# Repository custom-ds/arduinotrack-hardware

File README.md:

# ArduinoTrack APRS Tracker
The Project: Traveler ArduinoTrack flight controller is an Arduino-compatible board that includes a GPS, temp/pressure sensor, and options for a VHF transmitter module or a off-board transmitter.

For more information about the ArduinoTrack, visit the [Project: Traveler](https://www.projecttraveler.org/arduinotrack/arduinotrack-controller) website.

Firmware for the ArduinoTrack must be programmed via a hardware programmer.

[ArduinoTrack Firmware](https://github.com/custom-ds/arduinotrack-firmware)

## Buy an ArduinoTrack
Assembled ArduinoTracks can be purchased online from [Custom Digital Services](https://www.customdigitalservices.net/high-altitude-ballooning/buy-an-arduinotrack).

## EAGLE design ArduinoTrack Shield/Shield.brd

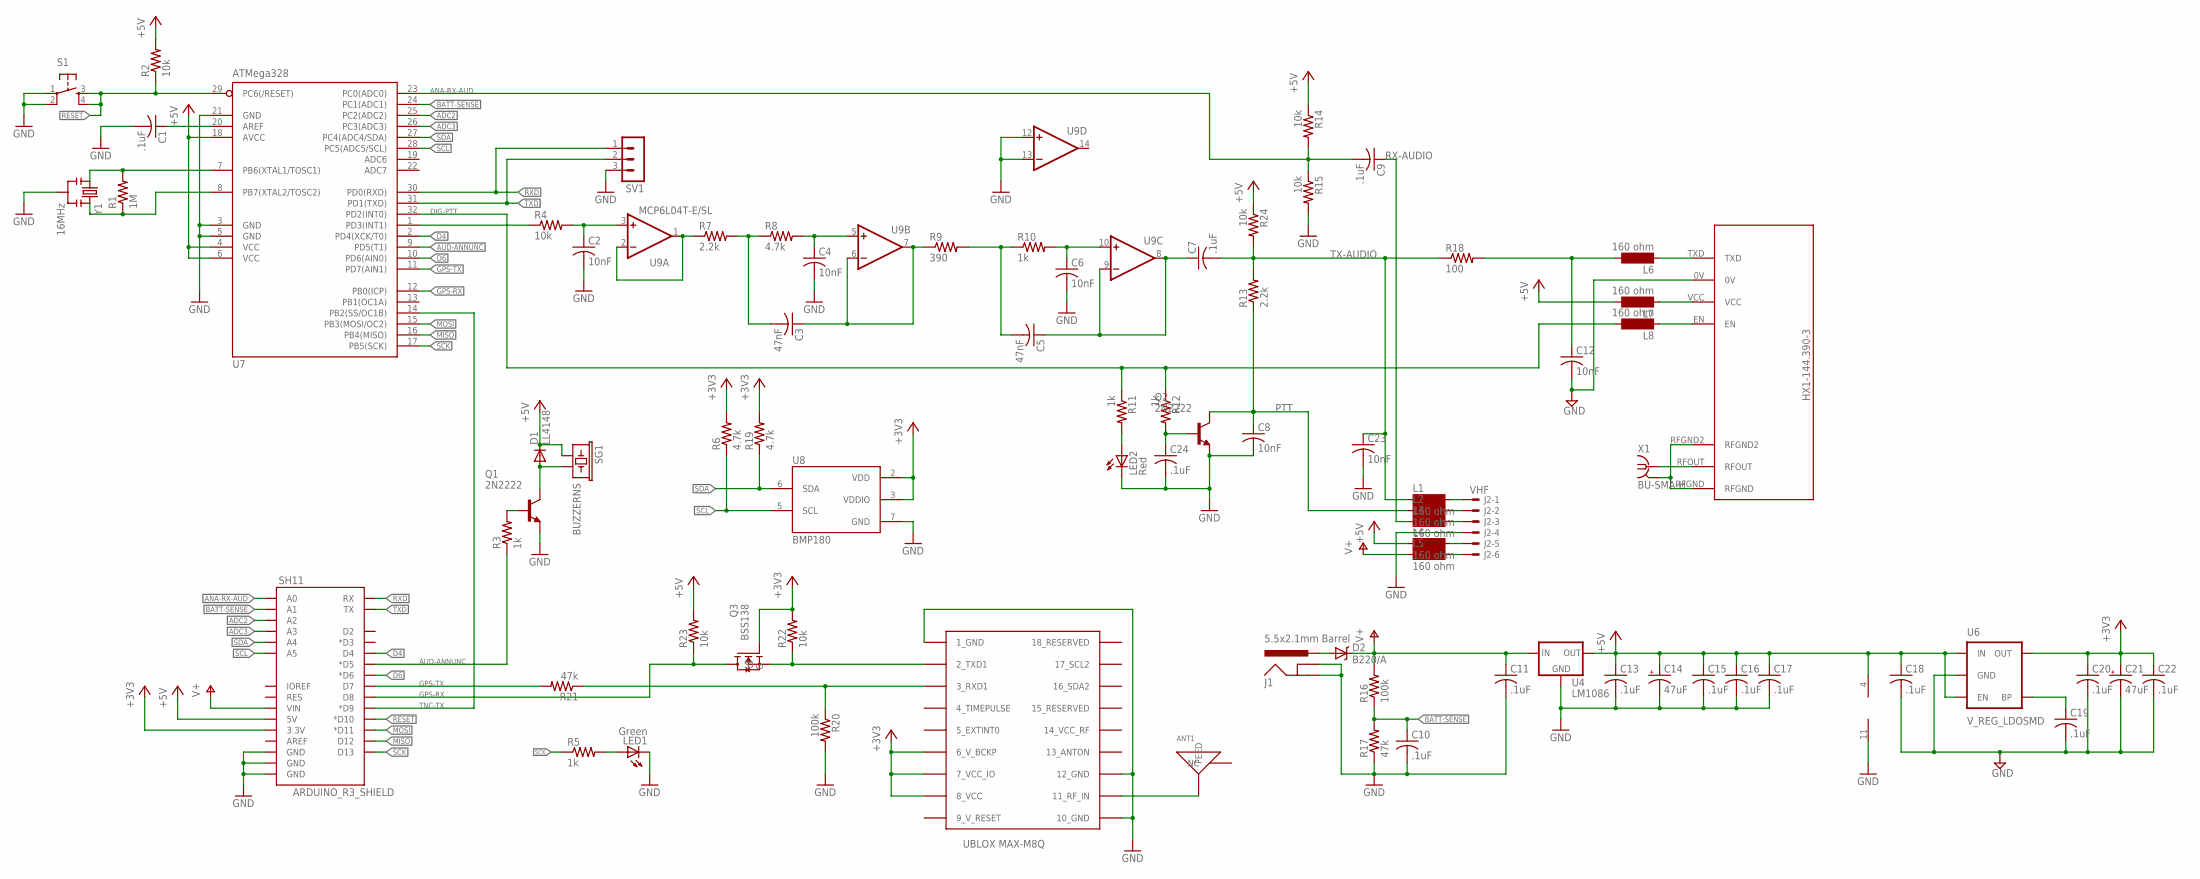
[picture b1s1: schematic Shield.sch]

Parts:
ANT1: GPS_ANT_SMDBAR; 1575AT43A40; DIGIKEY 712-1003-1-ND
C1, C7, C9, C10, C11, C13, C15, C16, C17, C18, C19, C20, C22, C24: .1uF; C0805; DIGIKEY 311-1361-1-ND
C2, C4, C6, C8, C12, C23: 10nF; C0805; DIGIKEY 399-1158-1-ND
C3, C5: 47nF; C0805; DIGIKEY 399-1166-1-ND
C14, C21: 47uF; 153CLV-0605; DIGIKEY PCE3842CT-ND
D1: LL4148; MINIMELF; DIGIKEY 568-1749-1-ND
D2: B220/A; SMA-DIODE; DIGIKEY 641-1258-1-ND
J1: 5.5x2.1mm Barrel; POWER_JACK_SMD; DIGIKEY CP-002AHPJCT-ND
J2: VHF; 7395-06; DIGIKEY WM4304-ND
L1, L2, L3, L4, L5, L6, L7, L8: 160 ohm; SM-1206; DIGIKEY 240-2411-1-ND
LED1: Green; CHIPLED_1206; DIGIKEY 160-1169-1-ND
LED2: Red; CHIPLED_1206; DIGIKEY 160-1405-1-ND
Q1, Q2: 2N2222; SOT23-BEC; DIGIKEY MMBT2222AFSCT-ND
Q3: BSS138; DIGIKEY BSS138CT-ND
R1: 1M; R0805; DIGIKEY 311-1.0MARCT-ND
R2, R4, R14, R15, R22, R23, R24: 10k; R0805; DIGIKEY 311-10.0KCRCT-ND
R3, R5, R10, R11, R12: 1k; R0805; DIGIKEY 311-1.0KARCT-ND
R6, R8, R19: 4.7k; R0805; DIGIKEY 311-4.7KARCT-ND
R7, R13: 2.2k; R0805; DIGIKEY 311-2.2KARCT-ND
R9: 390; R0805; DIGIKEY 311-390ARCT-ND
R16, R20: 100k; R0805; DIGIKEY 311-100KCRCT-ND
R17, R21: 47k; R0805; DIGIKEY 311-47.0KCRCT-ND
R18: 100; R0805; DIGIKEY 311-100ARCT-ND
S1: TAC_SWITCHSMD; TACTILE_SWITCH_SMD; DIGIKEY CKN9104CT-ND
SG1: BUZZERNS; BUZZER-12MM-NS; DIGIKEY 102-1155-ND
SH11: ARDUINO_R3_SHIELD; UNO_R3_SHIELD
SV1: MA03-1; DIGIKEY 952-2264-ND
U3: UBLOX_MAX
U4: LM1086; TO263; DIGIKEY LM1086ISX-5.0/NOPBCT-ND
U5: RADIOMETRIX-HX1
U6: V_REG_LDOSMD; SOT23-5; DIGIKEY LP3985IM5-3.3/NOPBCT-ND
U7: ATMega328; TQFP32-08; DIGIKEY ATMEGA328P-15AZCT-ND
U8: BMP180
U9: LMV324M; SO14; DIGIKEY MCP6L04T-E/SLCT-ND
X1: BU-SMA-H; DIGIKEY CONSMA001-ND
Y1: 16MHz; RESONATOR-SMD; DIGIKEY 478-5420-1-ND

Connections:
9_V_RESET: U3.9_V_RESET
+3V3: C20.1, C21.+, C22.1, Q3.G, R6.2, R19.2, R22.2, SH11.3.3V, U3.6_V_BCKP, U3.7_VCC_IO, U3.8_VCC, U6.5 (OUT), U8.2 (VDD), U8.3 (VDDIO)
+5V: C13.1, C14.+, C15.1, C16.1, C17.1, C18.1, D1.C, L4.1, L7.2, R2.2, R14.1, R23.2, R24.1, SG1.+ (1), SH11.5V, U4.2 (OUT), U6.1 (IN), U6.3 (EN), U7.4 (VCC), U7.6 (VCC), U7.18 (AVCC), U9.4 (V+)
ADC2: SH11.A2, U7.25 (PC2(ADC2))
ADC3: SH11.A3, U7.26 (PC3(ADC3))
ANA-RX-AUD: C9.2, R14.2, R15.1, SH11.A0, U7.23 (PC0(ADC0))
AUD-ANNUNC: R3.1, SH11.D5 (*D5), U7.9 (PD5(T1))
BATT-SENSE: C10.1, R16.1, R17.2, SH11.A1, U7.24 (PC1(ADC1))
D4: SH11.D4, U7.2 (PD4(XCK/T0))
D6: SH11.D6 (*D6), U7.10 (PD6(AIN0))
DIG-PTT: L8.2, R11.1, R12.1, U7.32 (PD2(INT0))
GND: C1.2, C2.2, C4.2, C6.2, C8.2, C10.2, C11.2, C12.2, C13.2, C14.-, C15.2, C16.2, C17.2, C18.2, C19.2, C20.2, C21.-, C22.2, C23.2, C24.2, J1.GND (GNDBREAK), J1.P$4 (GND), J2.4, LED1.C, LED2.C, Q1.E, Q2.E, R15.2, R17.1, R20.2, S1.1, S1.2, SH11.GND@0 (GND), SH11.GND@1 (GND), SH11.GND@2 (GND), SV1.3, U3.1_GND, U3.10_GND, U3.12_GND, U4.1 (GND), U5.0V, U6.2 (GND), U7.3 (GND), U7.5 (GND), U7.21 (GND), U8.7 (GND), U9.11 (V-), U9.12 (+IN), U9.13 (-IN), Y1.2
GPS-RX: Q3.D, R23.1, SH11.D8, U7.12 (PB0(ICP))
GPS-TX: R21.2, SH11.D7, U7.11 (PD7(AIN1))
MISO: SH11.D12, U7.16 (PB4(MISO))
MOSI: SH11.D11 (*D11), U7.15 (PB3(MOSI/OC2))
unnamed: C2.1, R4.2, U9.3 (+IN)
unnamed: R7.1, U9.1 (OUT), U9.2 (-IN)
unnamed: C3.2, R7.2, R8.1
unnamed: C4.1, R8.2, U9.5 (+IN)
unnamed: C3.1, R9.1, U9.6 (-IN), U9.7 (OUT)
unnamed: C5.2, R9.2, R10.1
unnamed: C6.1, R10.2, U9.10 (+IN)
unnamed: D2.A, J1.VIN0 (PWR)
unnamed: D1.A, Q1.C, SG1.- (2)
unnamed: C12.1, L6.2, R18.2
unnamed: C5.1, C7.1, U9.8 (OUT), U9.9 (-IN)
unnamed: U5.RFOUT, X1.1
unnamed: R4.1, U7.1 (PD3(INT1))
unnamed: Q3.S, R22.1, U3.2_TXD1
unnamed: R20.1, R21.1, U3.3_RXD1
unnamed: ANT1.FEED, U3.11_RF_IN
unnamed: R1.1, U7.8 (PB7(XTAL2/TOSC2)), Y1.3
unnamed: C24.1, Q2.B, R12.2
unnamed: LED2.A, R11.2
unnamed: LED1.A, R5.2
unnamed: Q1.B, R3.2
unnamed: L6.1, U5.TXD
unnamed: L7.1, U5.VCC
unnamed: L8.1, U5.EN
unnamed: J2.1, L1.2
unnamed: J2.2, L2.2
unnamed: J2.3, L3.2
unnamed: J2.5, L4.2
unnamed: J2.6, L5.2
unnamed: C1.1, U7.20 (AREF)
unnamed: C19.1, U6.4 (BP)
unnamed: R1.2, U7.7 (PB6(XTAL1/TOSC1)), Y1.1
PTT: C8.1, L2.1, Q2.C, R13.1
RESET: R2.1, S1.3, S1.4, SH11.D10 (*D10), U7.29 (PC6(/RESET))
RFGND: U5.RFGND, U5.RFGND2, X1.2, X1.3 (2), X1.4 (2), X1.5 (2)
RX-AUDIO: C9.1, L3.1
RXD: SH11.RX, SV1.1, U7.30 (PD0(RXD))
SCK: R5.1, SH11.D13, U7.17 (PB5(SCK))
SCL: R6.1, SH11.A5, U7.28 (PC5(ADC5/SCL)), U8.5 (SCL)
SDA: R19.1, SH11.A4, U7.27 (PC4(ADC4/SDA)), U8.6 (SDA)
TNC-TX: SH11.D9 (*D9), U7.14 (PB2(SS/OC1B))
TX-AUDIO: C7.2, C23.1, L1.1, R13.2, R18.1, R24.2
TXD: SH11.TX, SV1.2, U7.31 (PD1(TXD))
V+: C11.1, D2.C, L5.1, R16.2, SH11.VIN, U4.3 (IN)

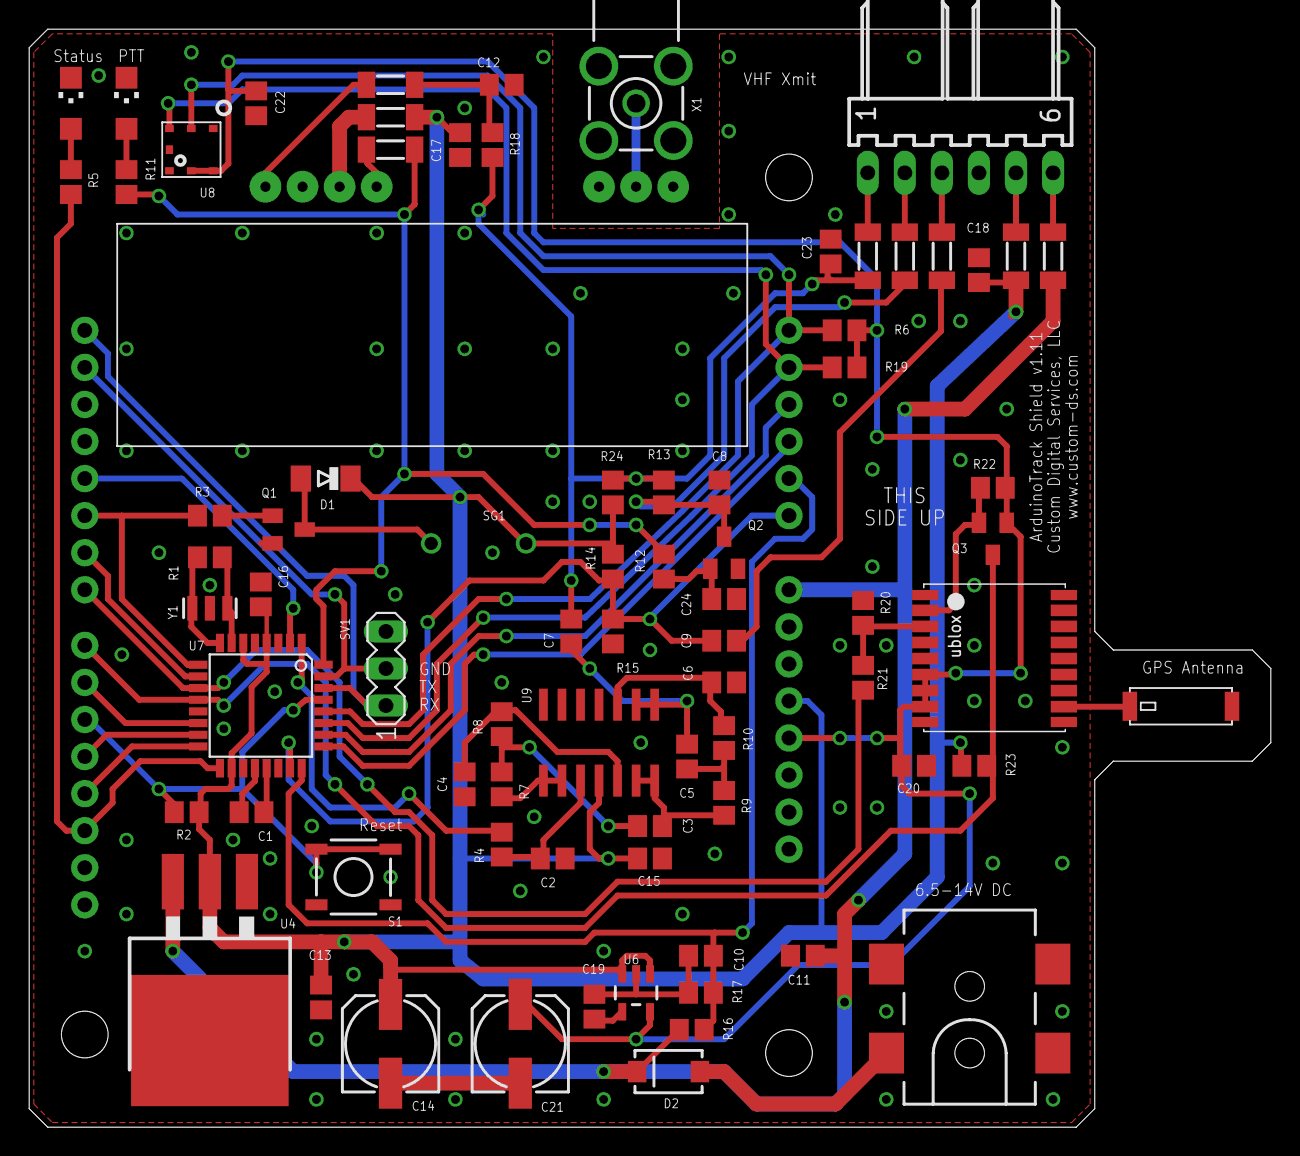
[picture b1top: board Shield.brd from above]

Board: 2 copper layers, 85.1 x 75.2 mm, 79 parts (0 on the bottom side), 59 nets.

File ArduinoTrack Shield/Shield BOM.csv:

"Qty";"Value";"Device";"Package";"Parts";"Description";"DIGIKEY";"MF";"MPN";"OC_FARNELL";"OC_NEWARK";"PROD_ID";"VALUE";
"1";"";"MA03-1";"MA03-1";"SV1";"PIN HEADER";"";"";"";"unknown";"unknown";"";"";
"1";"";"TAC_SWITCHSMD";"TACTILE_SWITCH_SMD";"S1";"Momentary Switch";"CKN9104CT-ND";"";"";"";"";"SWCH-08247";"";
"13";".1uF";"C-USC0805";"C0805";"C1, C7, C9, C10, C11, C13, C15, C16, C17, C18, C19, C20, C22";"CAPACITOR, American symbol";"311-1361-1-ND";"";"";"";"";"";"";
"1";"100";"R-US_R0805";"R0805";"R18";"RESISTOR, American symbol";"311-100ARCT-ND";"";"";"";"";"";"";
"2";"100k";"R-US_R0805";"R0805";"R16, R20";"RESISTOR, American symbol";"311-100KCRCT-ND";"";"";"";"";"";"";
"6";"10k";"R-US_R0805";"R0805";"R2, R4, R14, R15, R22, R23";"RESISTOR, American symbol";"311-10.0KCRCT-ND";"";"";"";"";"";"";
"5";"10nF";"C-USC0805";"C0805";"C2, C4, C6, C8, C12";"CAPACITOR, American symbol";"399-1158-1-ND";"";"";"";"";"";"";
"8";"160 ohm";"SM-1206";"SM-1206";"L1, L2, L3, L4, L5, L6, L7, L8";"INDUCTOR";"240-2411-1-ND";"";"";"unknown";"unknown";"";"";
"1";"16MHz";"RESONATOR16MHZ";"RESONATOR-SMD";"Y1";"Resonator";"478-5420-1-ND";"";"";"";"";"XTAL-08900";"16MHz";
"1";"1M";"R-US_R0805";"R0805";"R1";"RESISTOR, American symbol";"311-1.0MARCT-ND";"";"";"";"";"";"";
"5";"1k";"R-US_R0805";"R0805";"R3, R5, R10, R11, R12";"RESISTOR, American symbol";"311-1.0KARCT-ND";"";"";"";"";"";"";
"2";"2.2k";"R-US_R0805";"R0805";"R7, R13";"RESISTOR, American symbol";"311-2.2KARCT-ND";"";"";"";"";"";"";
"2";"2N2222";"BC817-16LT1SMD";"SOT23-BEC";"Q1, Q2";"NPN Transistor";"MMBT2222AFSCT-ND";"";"";"";"";"";"";
"1";"390";"R-US_R0805";"R0805";"R9";"RESISTOR, American symbol";"311-390ARCT-ND";"";"";"";"";"";"";
"3";"4.7k";"R-US_R0805";"R0805";"R6, R8, R19";"RESISTOR, American symbol";"311-4.7KARCT-ND";"";"";"";"";"";"";
"2";"47k";"R-US_R0805";"R0805";"R17, R21";"RESISTOR, American symbol";"311-47.0KCRCT-ND";"";"";"";"";"";"";
"2";"47nF";"C-USC0805";"C0805";"C3, C5";"CAPACITOR, American symbol";"399-1166-1-ND";"";"";"";"";"";"";
"2";"47uF";"CPOL-US153CLV-0605";"153CLV-0605";"C14, C21";"POLARIZED CAPACITOR, American symbol";"PCE3842CT-ND";"";"";"";"";"";"";
"1";"5.5x2.1mm Barrel";"POWER_JACKSMD";"POWER_JACK_SMD";"J1";"Power Jack";"CP-002AHPJCT-ND";"";"";"";"";"CONN-08106";"5.5x2.1mm Barrel";
"1";"ARDUINO_R3_SHIELD";"ARDUINO_R3_SHIELD";"UNO_R3_SHIELD";"SH11";"Shield form compatible with the Arduino Uno R3.";"SAM1112-32-ND";"";"";"";"";"";"";
"1";"ATMega328";"MEGA8-AI";"TQFP32-08";"U7";"MICROCONTROLLER";"ATMEGA328P-15AZCT-ND";"";"ATMEGA8-16AU";"9171371";"73M8863";"";"";
"1";"B220/A";"B340A";"SMA-DIODE";"D2";"Schottky Diode";"641-1258-1-ND";"";"";"";"";"DIO-09886";"BA340A";
"1";"BMP180";"BMP180";"BMP180";"U8";"BOSCH BMP180 DIGITAL BAROMETRIC PRESSURE SENSOR";"828-1027-1-ND";"";"";"";"";"";"";
"1";"BSS138";"BSS138";"BSS138";"U$1";"BSS138";"BSS138CT-ND";"";"";"";"";"";"";
"1";"BU-SMA-H";"BU-SMA-H";"BU-SMA-H";"X1";"FEMALE SMA CONNECTOR";"CONSMA002-G-ND";"";"";"unknown";"unknown";"";"";
"1";"BUZZERNS";"BUZZERNS";"BUZZER-12MM-NS";"SG1";"Buzzer 12mm";"102-1155-ND";"";"";"";"";"";"";
"1";"GPS_ANT_SMDBAR";"GPS_ANT_SMDBAR";"1575AT43A40";"ANT1";"1.575 GHz GPS Antenna Johanson Technology";"712-1003-1-ND";"";"";"";"";"";"";
"1";"Green";"LEDCHIPLED_1206";"CHIPLED_1206";"LED1";"LED";"160-1169-1-ND";"";"";"";"";"";"";
"1";"LL4148";"DIODE-MINIMELF";"MINIMELF";"D1";"DIODE";"568-1749-1-ND";"";"";"";"";"";"";
"1";"LM1086";"LM1086TO263";"TO263";"U4";"";"LM1086ISX-5.0/NOPBCT-ND";"";"";"";"";"";"";
"1";"LMV324M";"LMV324M";"SO14";"U9";"Quad General Purpose, Low Voltage, Rail-to-Rail Output Operational Amplifiers";"LT1679CS#PBF-ND";"";"";"";"";"";"";
"1";"RADIOMETRIX-HX1";"RADIOMETRIX-HX1";"RADIOMETRIX-HX1";"U5";"";"";"";"";"";"";"";"";
"1";"Red";"LEDCHIPLED_1206";"CHIPLED_1206";"LED2";"LED";"160-1405-1-ND";"";"";"";"";"";"";
"1";"UBLOX_MAX";"UBLOX_MAX";"UBLOX_MAX";"U3";"UBLOX MAX";"";"";"";"";"";"";"";
"1";"VHF";"22-05-7068-06";"7395-06";"J2";"CONNECTOR";"WM4304-ND";"";"";"unknown";"unknown";"";"";
"1";"V_REG_LDOSMD";"V_REG_LDOSMD";"SOT23-5";"U6";"Voltage Regulator LDO";"LP3985IM5-3.3/NOPBCT-ND";"";"";"";"";"";"";

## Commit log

2016-01-26 Initial commit
    Initial commit of the ArduinoTrack PCB hardware after splitting the
    firmware and hardware repos. The current hardware version is v1.11
    which uses the BMP-180 temp/pressure sensor, as well as the uBlox Max
    M8Q GPS engine.
2016-02-08 Minor clean up work to schematic
    Added some values to parts, swapped out the op-amp with a cheaper
    alternative, added part numbers to HX1 and Ublox GPS. Generated a fresh
    BOM, and cleaned up some old files.
2016-04-10 Working on assembly instructions
2018-12-28 Updating readme.

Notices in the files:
parts and their libraries:
sparkfun-boards: Licensing: CC v3.0 Share-Alike You are welcome to use this library for commercial purposes.
